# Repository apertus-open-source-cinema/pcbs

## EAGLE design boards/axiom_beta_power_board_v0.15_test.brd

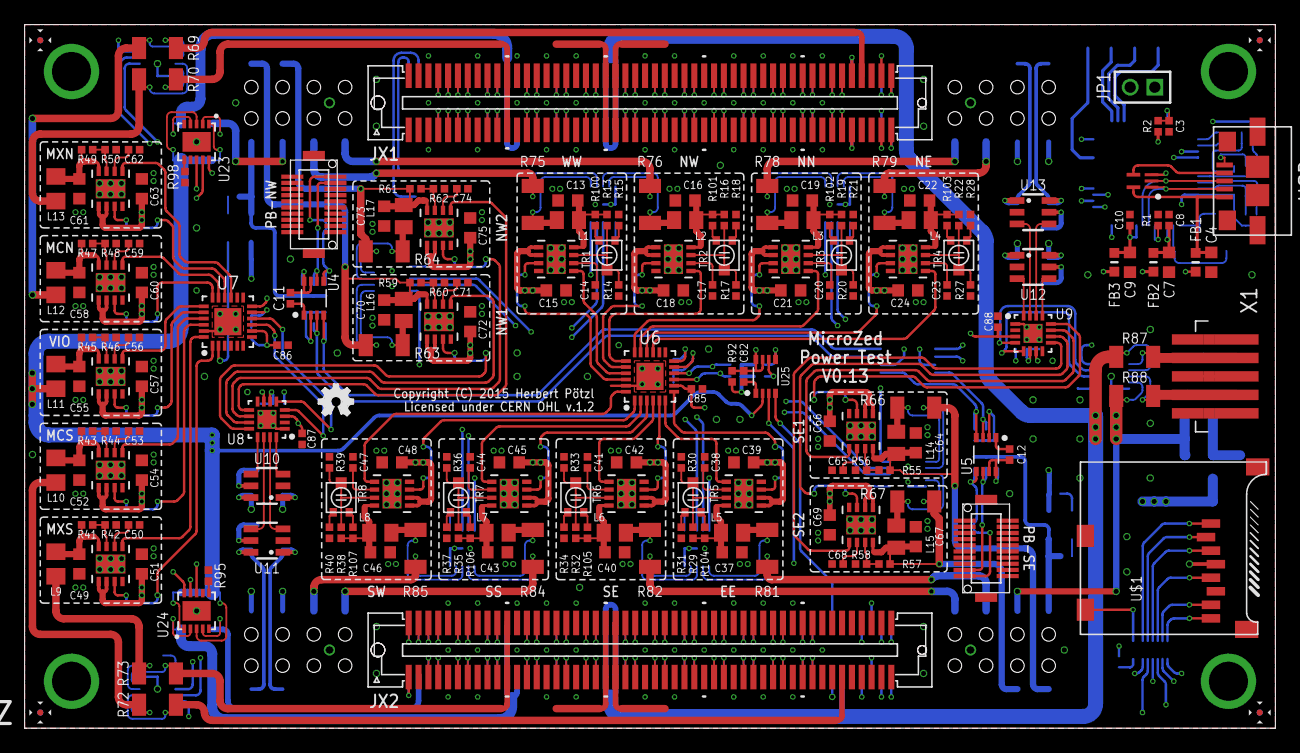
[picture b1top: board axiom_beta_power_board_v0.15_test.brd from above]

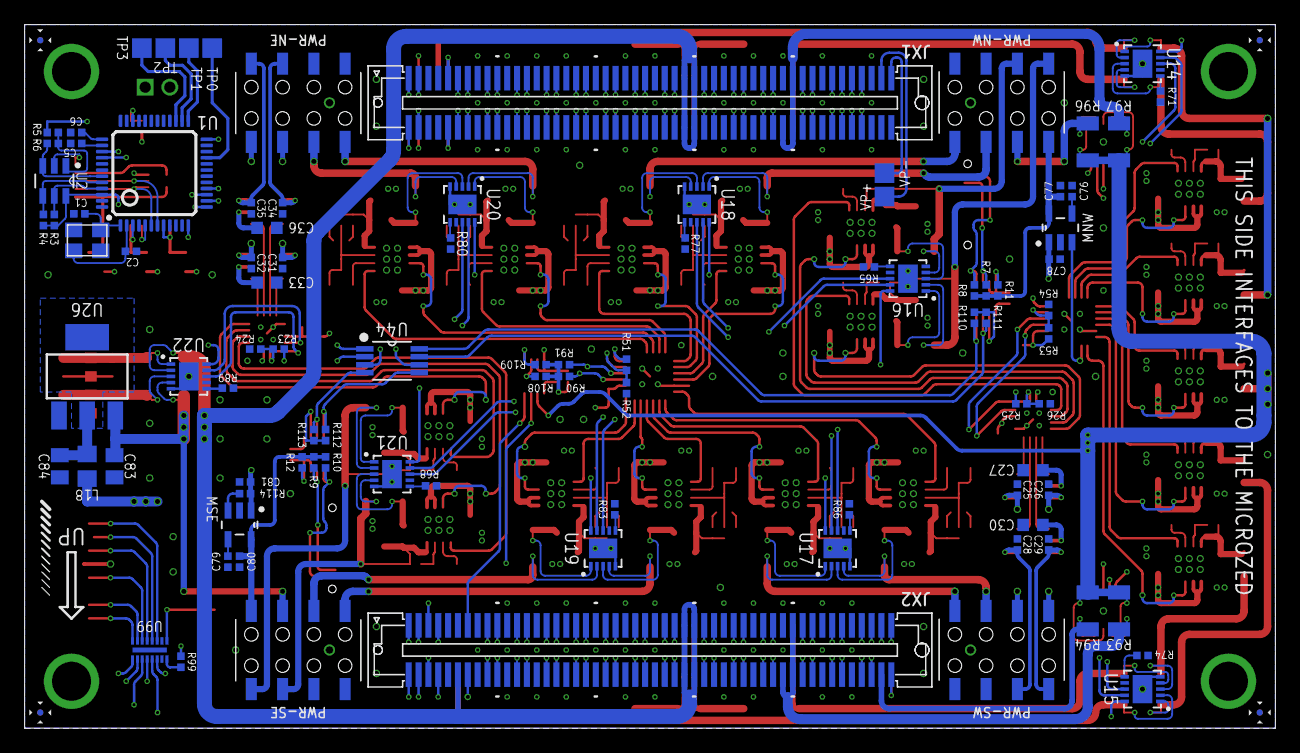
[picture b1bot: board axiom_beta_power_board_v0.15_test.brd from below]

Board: 4 copper layers, 101.6 x 57.1 mm, 298 parts (94 on the bottom side), 361 nets.

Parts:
BETA: µZ-FCI-SOCKET-NOHOLES-R; µZ-SOCKET-NOHOLES-R
C1, C2, C11, C12, C14, C17, C20, C23, C38, C41, C44, C47, C50, C53, C56, C59, C62, C65, C68, C71, C74, C76, C77, C78, C79, C80, C81, C82, C85, C86, C87, C88: 0402-B
C3: 10n; 0402-B
C4: 100n; 0603-B
C5, C6, C8, C10: 100n; 0402-B
C7, C9: 4µ7; 0603-B
C13, C15, C16, C18, C19, C21, C22, C24, C37, C39, C40, C42, C43, C45, C46, C48, C49, C51, C52, C54, C55, C57, C58, C60, C61, C63, C64, C66, C67, C69, C70, C72, C73, C75: 0603-B
C25, C26, C28, C29, C31, C32, C34, C35: 1µ; 0402-B
C27, C30, C33, C36: 1µ; 0603-B
C83, C84: 0805-B
EE: MCP1727-ADJE/MF; DFN65P300X300X100-9N
FB1, FB2, FB3: 600R; _0603MP
JP1: 1X02M
L1, L2, L3, L4, L5, L6, L7, L8, L14, L15, L16, L17: 0805-B
L9, L10, L11, L12, L13, L18: 0805-A
LOGO1: OSHW_LOGO_FILLX0100-NT; OSHW_FILLX100_NOTEXT
MCN: MCP1727-ADJE/MF; DFN65P300X300X100-9N
MCS: MCP1727-ADJE/MF; DFN65P300X300X100-9N
MNW: SPX3819M5-L; SOT95P280X145-5N
MSE: SPX3819M5-L; SOT95P280X145-5N
MXN: MCP1727-ADJE/MF; DFN65P300X300X100-9N
MXS: MCP1727-ADJE/MF; DFN65P300X300X100-9N
NE: MCP1727-ADJE/MF; DFN65P300X300X100-9N
NN: MCP1727-ADJE/MF; DFN65P300X300X100-9N
NW, NW1, NW2: MCP1727-ADJE/MF; DFN65P300X300X100-9N
PB-NW: DF12(XX)-20DP-0.5V
PB-SE: DF12(XX)-20DP-0.5V
PWR-NE: PINRC-2X04; R2X04
PWR-NW: PINRC-2X04; R2X04
PWR-SE: PINRC-2X04; R2X04
PWR-SW: PINRC-2X04; R2X04
Q1: SMD-4P-2G-3.2X2.5; ABM8G
R1: 12k; 0402-B
R2, R3, R4, R5: 10k; 0402-B
R6: 2k; 0402-B
R7, R8, R9, R10, R11, R12, R13, R14, R15, R16, R17, R18, R19, R20, R21, R22, R23, R24, R25, R26, R27, R28, R29, R30, R31, R32, R33, R34, R35, R36, R37, R38, R39, R40, R41, R42, R43, R44, R45, R46, R47, R48, R49, R50, R51, R52, R53, R54, R55, R56, R57, R58, R59, R60, R61, R62, R65, R68, R71, R74, R77, R80, R83, R86, R89, R90, R91, R92, R95, R98, R99, R100, R101, R102, R103, R104, R105, R106, R107, R108, R109, R110, R111, R112, R113, R114: 0402-B
R63, R64, R66, R67, R69, R70, R72, R73, R75, R76, R78, R79, R81, R82, R84, R85, R87, R88, R93, R94, R96, R97: 1206-B
SE, SE1, SE2: MCP1727-ADJE/MF; DFN65P300X300X100-9N
SS: MCP1727-ADJE/MF; DFN65P300X300X100-9N
SW: MCP1727-ADJE/MF; DFN65P300X300X100-9N
TP0, TP1, TP2, TP3: TPTP16SQ; TP16SQ
TR1, TR2, TR3, TR4, TR5, TR6, TR7, TR8: PVZ2A; TRIM-PVZ2A
U1: FT232H; LQFP48
U2: 93LC46BT-I/OT; SOT95P280X145-6N
U3: TPD3E001DRLR; SOT50P160X60-5N
U4, U5, U25: GTL2002DC; VSSOP-8
U6, U7: QFN50P400X400X80-25N
U8, U9: MCP23009-E/MG; QFN50P300X300X80-17N
U10, U11, U12, U13: SOT23-6
U14, U15, U16, U17, U18, U19, U20, U21, U22, U23, U24: PAC1720; DFN3X3_10LEAD
U26: LD1117S; SOT-223
U44: PCA9540BDP; SOP65P490X110-8N
U99: IP4251CZ16-8-TTL; SON40P135X330X55-17N
U$1: MICRO-SD-2CD; TF-MICRO-SD_PP2
USB: 5_USB_3S; MICRO-AB-H-SMT
VIO: MCP1727-ADJE/MF; DFN65P300X300X100-9N
VP+: TPTP16SQ; TP16SQ
VP-: TPTP16SQ; TP16SQ
WW: MCP1727-ADJE/MF; DFN65P300X300X100-9N
X1: PICO-SPOX-5
ZED: µZ-FCI-CONONLY; µZ-CONONLY

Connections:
AB_SCL: U25.4, ZED.113
AB_SCL': R109.2, U25.5, U44.1
AB_SDA: U25.3, ZED.114
AB_SDA': R108.2, U25.6, U44.2
A_SCL: PB-NW.2, R8.2, U4.5
A_SCL': R110.2, U4.4, U44.8
A_SDA: PB-NW.4, R7.2, U4.6
A_SDA': R111.2, U4.3, U44.7
BANK13_00_N: BETA.87, ZED.87
BANK13_00_P: BETA.89, ZED.89
BANK13_01_N: BETA.90, ZED.90
BANK13_01_P: BETA.88, ZED.88
BANK13_02_N: BETA.91, ZED.91
BANK13_02_P: BETA.93, ZED.93
BANK13_03_N: BETA.92, ZED.92
BANK13_03_P: BETA.94, ZED.94
BANK13_04_N: BETA.193, ZED.193
BANK13_04_P: BETA.195, ZED.195
BANK13_05_N: BETA.196, ZED.196
BANK13_05_P: BETA.194, ZED.194
BANK13_06_N: BETA.199, ZED.199
BANK13_06_P: BETA.197, ZED.197
BANK13_SE_0: BETA.200, ZED.200
BETA_5V: R88.1, U22.3, X1.4, X1.4A
BETA_5V': C15.1, C18.1, C21.1, C24.1, C27.1, C30.1, C33.1, C36.1, C39.1, C42.1, C45.1, C48.1, C51.1, C54.1, C57.1, C60.1, C63.1, C66.1, C69.1, C72.1, C75.1, C78.1, C81.1, C83.1, EE.1, EE.2, MCN.1, MCN.2, MCS.1, MCS.2, MNW.1, MSE.1, MXN.1, MXN.2, MXS.1, MXS.2, NE.1, NE.2, NN.1, NN.2, NW.1, NW.2, NW1.1, NW1.2, NW2.1, NW2.2, PWR-SE.6, R88.2, R114.1, SE.1, SE.2, SE1.1, SE1.2, SE2.1, SE2.2, SS.1, SS.2, SW.1, SW.2, U10.5, U11.5, U12.5, U13.5, U22.4, U26.3, VIO.1, VIO.2, WW.1, WW.2
BETA_TDO: BETA.3, JP1.2
B_SCL: PB-SE.2, R10.2, U5.5
B_SCL': R112.2, U5.4, U44.5
B_SDA: PB-SE.4, R9.2, U5.6
B_SDA': R113.2, U5.3, U44.4
CD: U99.1, U$1.CD1
CLK: U99.6, U$1.5
CMD: U99.5, U$1.3
CSO_N_V: BETA.7, R69.2, U14.2
CSO_N_V': L12.2, R69.1, U14.1
CSO_S_V: BETA.112, R72.2, U15.2
CSO_S_V': L10.2, R72.1, U15.1
DAT0: U99.7, U$1.7
DAT1: U99.8, U$1.8
DAT2: U99.3, U$1.1
DAT3: U99.4, U$1.2
EE_CLK1: R4.1, U1.44, U2.4
EE_CS1: R3.1, U1.45, U2.5
EE_DATA1: R6.2, U1.43, U2.3
EN1: U8.13, U10.4
EN1B: U9.13, U12.4
EN2: U8.14, U11.4
EN2B: U9.14, U13.4
EN3: U8.16, U10.3
EN3B: U9.16, U12.3
EN4: U8.15, U11.3
EN4B: U9.15, U13.3
EX_N_V: BETA.57, BETA.58
EX_S_V: BETA.157, BETA.158
E_I2C_V: C34.1, PWR-NE.6, U13.1
E_SPI_V: C35.1, PWR-NE.8, U13.6
E_VE: PWR-SE.4, R81.2, U19.2
E_VE': L5.2, R81.1, U19.1
FTDI_D_N: U1.6, U3.1, USB.2
FTDI_D_P: U1.7, U3.2, USB.3
FTDI_TCK: BETA.1, U1.13, ZED.1
FTDI_TDI: BETA.4, U1.14
FTDI_TDO: U1.15, ZED.3
FTDI_TMS: BETA.2, U1.16, ZED.2
GND: BETA.15, BETA.16, BETA.21, BETA.22, BETA.27, BETA.28, BETA.33, BETA.34, BETA.39, BETA.40, BETA.45, BETA.46, BETA.51, BETA.52, BETA.65, BETA.66, BETA.71, BETA.72, BETA.77, BETA.85, BETA.86, BETA.95, BETA.96, BETA.115, BETA.116, BETA.121, BETA.122, BETA.127, BETA.128, BETA.133, BETA.134, BETA.139, BETA.140, BETA.145, BETA.146, BETA.151, BETA.152, BETA.165, BETA.166, BETA.171, BETA.172, BETA.177, BETA.185, BETA.186, BETA.191, BETA.192, C1.2, C2.2, C3.2, C4.2, C5.2, C6.2, C7.2, C8.2, C9.2, C10.2, C11.2, C12.2, C13.2, C14.2, C15.2, C16.2, C17.2, C18.2, C19.2, C20.2, C21.2, C22.2, C23.2, C24.2, C25.2, C26.2, C27.2, C28.2, C29.2, C30.2, C31.2, C32.2, C33.2, C34.2, C35.2, C36.2, C37.2, C38.2, C39.2, C40.2, C41.2, C42.2, C43.2, C44.2, C45.2, C46.2, C47.2, C48.2, C49.2, C50.2, C51.2, C52.2, C53.2, C54.2, C55.2, C56.2, C57.2, C58.2, C59.2, C60.2, C61.2, C62.2, C63.2, C64.2, C65.2, C66.2, C67.2, C68.2, C69.2, C70.2, C71.2, C72.2, C73.2, C74.2, C75.2, C76.2, C77.2, C78.2, C79.2, C80.2, C81.2, C82.2, C83.2, C84.2, C85.2, C86.2, C87.2, C88.2, EE.4, EE.9, MCN.4, MCN.9, MCS.4, MCS.9, MNW.2, MSE.2, MXN.4, MXN.9, MXS.4, MXS.9, NE.4, NE.9, NN.4, NN.9, NW.4, NW.9, NW1.4, NW1.9, NW2.4, NW2.9, PB-NW.6, PB-NW.7, PB-NW.10, PB-NW.13, PB-NW.18, PB-SE.6, PB-SE.7, PB-SE.10, PB-SE.13, PB-SE.18, PWR-NE.2, PWR-NE.4, PWR-NW.1, PWR-NW.3, PWR-SE.1, PWR-SE.3, PWR-SW.2, PWR-SW.4, Q1.2, Q1.4, R1.1, R14.2, R15.2, R17.2, R18.2, R20.2, R21.2, R24.2, R26.2, R27.2, R28.2, R30.2, R31.2, R33.2, R34.2, R36.2, R37.2, R39.2, R40.2, R42.2, R44.2, R46.2, R48.2, R50.2, R52.2, R54.2, R56.2, R58.2, R60.2, R62.2, R65.2, R68.2, R71.2, R74.2, R77.2, R80.2, R83.2, R86.2, R89.2, R95.2, R98.2, SE.4, SE.9, SE1.4, SE1.9, SE2.4, SE2.9, SS.4, SS.9, SW.4, SW.9, U1.4, U1.9, U1.10, U1.11, U1.22, U1.23, U1.35, U1.36, U1.41, U1.47, U1.48, U2.2, U3.3, U4.1, U5.1, U6.23, U6.25, U7.23, U7.25, U8.1, U8.EP, U9.1, U9.EP, U10.2, U11.2, U12.2, U13.2, U14.5, U14.EPAD, U15.5, U15.EPAD, U16.5, U16.EPAD, U17.5, U17.EPAD, U18.5, U18.EPAD, U19.5, U19.EPAD, U20.5, U20.EPAD, U21.5, U21.EPAD, U22.5, U22.EPAD, U23.5, U23.EPAD, U24.5, U24.EPAD, U25.1, U26.1, U44.6, U99.17, U$1.6, U$1.CD2, USB.5, VIO.4, VIO.9, WW.4, WW.9, X1.1, X1.1A, X1.5, X1.5A, ZED.15, ZED.16, ZED.21, ZED.22, ZED.27, ZED.28, ZED.33, ZED.34, ZED.39, ZED.40, ZED.45, ZED.46, ZED.51, ZED.52, ZED.65, ZED.66, ZED.71, ZED.72, ZED.77, ZED.85, ZED.86, ZED.95, ZED.96, ZED.115, ZED.116, ZED.121, ZED.122, ZED.127, ZED.128, ZED.133, ZED.134, ZED.139, ZED.140, ZED.145, ZED.146, ZED.151, ZED.152, ZED.165, ZED.166, ZED.171, ZED.172, ZED.177, ZED.185, ZED.186, ZED.191, ZED.192
GPA0_C: NE.5, U6.15
GPA0_W: MXN.5, U7.15
GPA1_C: NE.3, U6.16
GPA1_W: MXN.3, U7.16
GPA2_C: NN.5, U6.17
GPA2_W: MCN.5, U7.17
GPA3_C: NN.3, U6.18
GPA3_W: MCN.3, U7.18
GPA4_C: NW.5, U6.19
GPA4_W: U7.19, VIO.5
GPA5_C: NW.3, U6.20
GPA5_W: U7.20, VIO.3
GPA6_C: U6.21, WW.5
GPA6_W: MCS.5, U7.21
GPA7_C: U6.22, WW.3
GPA7_W: MCS.3, U7.22
GPB0_C: SW.5, U6.24
GPB0_W: MXS.5, U7.24
GPB1_C: SW.3, U6.1
GPB1_W: MXS.3, U7.1
GPB2_C: SS.5, U6.2
GPB2_W: MNW.3, U7.2
GPB3_C: SS.3, U6.3
GPB4_C: SE.5, U6.4
GPB5_C: SE.3, U6.5
GPB6_C: EE.5, U6.6
GPB7_C: EE.3, U6.7
JTAG_V: C29.1, PWR-SW.8, U11.6
JX1_00_N: BETA.13, ZED.13
JX1_00_P: BETA.11, ZED.11
JX1_01_N: BETA.14, ZED.14
JX1_01_P: BETA.12, ZED.12
JX1_02_N: BETA.19, ZED.19
JX1_02_P: BETA.17, ZED.17
JX1_03_N: BETA.20, ZED.20
JX1_03_P: BETA.18, ZED.18
JX1_04_N: BETA.25, ZED.25
JX1_04_P: BETA.23, ZED.23
JX1_05_N: BETA.26, ZED.26
JX1_05_P: BETA.24, ZED.24
JX1_06_N: BETA.31, ZED.31
JX1_06_P: BETA.29, ZED.29
JX1_07_N: BETA.32, ZED.32
JX1_07_P: BETA.30, ZED.30
JX1_08_N: BETA.37, ZED.37
JX1_08_P: BETA.35, ZED.35
JX1_09_N: BETA.38, ZED.38
JX1_09_P: BETA.36, ZED.36
JX1_10_N: BETA.43, ZED.43
JX1_10_P: BETA.41, ZED.41
JX1_11_N: BETA.44, ZED.44
JX1_11_P: BETA.42, ZED.42
JX1_12_N: BETA.49, ZED.49
JX1_12_P: BETA.47, ZED.47
JX1_13_N: BETA.50, ZED.50
JX1_13_P: BETA.48, ZED.48
JX1_14_N: BETA.55, ZED.55
JX1_14_P: BETA.53, ZED.53
JX1_15_N: BETA.56, ZED.56
JX1_15_P: BETA.54, ZED.54
JX1_16_N: BETA.63, ZED.63
JX1_16_P: BETA.61, ZED.61
JX1_17_N: BETA.64, ZED.64
JX1_17_P: BETA.62, ZED.62
JX1_18_N: BETA.69, ZED.69
JX1_18_P: BETA.67, ZED.67
JX1_19_N: BETA.70, ZED.70
JX1_19_P: BETA.68, ZED.68
JX1_20_N: BETA.75, ZED.75
JX1_20_P: BETA.73, ZED.73
JX1_21_N: BETA.76, ZED.76
JX1_21_P: BETA.74, ZED.74
JX1_22_N: BETA.83, ZED.83
JX1_22_P: BETA.81, ZED.81
JX1_23_N: BETA.84, ZED.84
JX1_23_P: BETA.82, ZED.82
JX2_00_N: BETA.119, ZED.119
JX2_00_P: BETA.117, ZED.117
JX2_01_N: BETA.120, ZED.120
JX2_01_P: BETA.118, ZED.118
JX2_02_N: BETA.125, ZED.125
JX2_02_P: BETA.123, ZED.123
JX2_03_N: BETA.126, ZED.126
JX2_03_P: BETA.124, ZED.124
JX2_04_N: BETA.131, ZED.131
JX2_04_P: BETA.129, ZED.129
JX2_05_N: BETA.132, ZED.132
JX2_05_P: BETA.130, ZED.130
JX2_06_N: BETA.137, ZED.137
JX2_06_P: BETA.135, ZED.135
JX2_07_N: BETA.138, ZED.138
JX2_07_P: BETA.136, ZED.136
JX2_08_N: BETA.143, ZED.143
JX2_08_P: BETA.141, ZED.141
JX2_09_N: BETA.144, ZED.144
JX2_09_P: BETA.142, ZED.142
JX2_10_N: BETA.149, ZED.149
JX2_10_P: BETA.147, ZED.147
JX2_11_N: BETA.150, ZED.150
JX2_11_P: BETA.148, ZED.148
JX2_12_N: BETA.155, ZED.155
JX2_12_P: BETA.153, ZED.153
JX2_13_N: BETA.156, ZED.156
JX2_13_P: BETA.154, ZED.154
JX2_14_N: BETA.163, ZED.163
JX2_14_P: BETA.161, ZED.161
JX2_15_N: BETA.164, ZED.164
JX2_15_P: BETA.162, ZED.162
JX2_16_N: BETA.169, ZED.169
JX2_16_P: BETA.167, ZED.167
JX2_17_N: BETA.170, ZED.170
JX2_17_P: BETA.168, ZED.168
JX2_18_N: BETA.175, ZED.175
JX2_18_P: BETA.173, ZED.173
JX2_19_N: BETA.176, ZED.176
JX2_19_P: BETA.174, ZED.174
JX2_20_N: BETA.183, ZED.183
JX2_20_P: BETA.181, ZED.181
JX2_21_N: BETA.184, ZED.184
JX2_21_P: BETA.182, ZED.182
JX2_22_N: BETA.189, ZED.189
JX2_22_P: BETA.187, ZED.187
JX2_23_N: BETA.190, ZED.190
JX2_23_P: BETA.188, ZED.188
MP-NW-1': L16.2, R63.1, U16.1
MP-NW-2': L17.2, R64.1, U16.3
MP-SE-1': L14.2, R66.1, U21.1
MP-SE-2': L15.2, R67.1, U21.3
M_V_NW: C77.1, MNW.5, PWR-NW.8, R7.1, R8.1, R11.1
M_V_SE: C80.1, MSE.5, PWR-SE.8, R9.1, R10.1, R12.1
unnamed: C49.1, L9.1, MXS.8, R41.1
unnamed: R77.1, U18.6
unnamed: C11.1, R11.2, U4.7, U4.8
unnamed: C12.1, R12.2, U5.7, U5.8
unnamed: C13.1, L1.1, R13.1, R100.2, WW.8
unnamed: TP1.TP, U1.25
unnamed: TP2.TP, U1.26
unnamed: R95.1, U24.6
unnamed: R13.2, R14.1, TR1.2, WW.7
unnamed: R15.1, TR1.1
unnamed: MXS.7, R41.2, R42.1
unnamed: C50.1, MXS.6
unnamed: C64.1, L14.1, R55.1, SE1.8
unnamed: R55.2, R56.1, SE1.7
unnamed: VP+.TP, ZED.97
unnamed: VP-.TP, ZED.99
unnamed: R98.1, U23.6
unnamed: TP3.TP, U1.27
unnamed: R99.2, U99.16
unnamed: C14.1, WW.6
unnamed: C65.1, SE1.6
unnamed: C67.1, L15.1, R57.1, SE2.8
unnamed: TP0.TP, U1.21
unnamed: R5.1, R6.1, U2.1
unnamed: C1.1, Q1.1, U1.1
unnamed: C2.1, Q1.3, U1.2
unnamed: C3.1, R2.1, U1.34
unnamed: R1.2, U1.5
unnamed: U3.4, USB.4
unnamed: R23.2, R24.1, U9.6
unnamed: R25.2, R26.1, U8.6
unnamed: R100.1, TR1.3
unnamed: C16.1, L2.1, NW.8, R16.1, R101.2
unnamed: NW.7, R16.2, R17.1, TR2.2
unnamed: R18.1, TR2.1
unnamed: C17.1, NW.6
unnamed: R57.2, R58.1, SE2.7
unnamed: C68.1, SE2.6
unnamed: R80.1, U20.6
unnamed: C19.1, L3.1, NN.8, R19.1, R102.2
unnamed: NN.7, R19.2, R20.1, TR3.2
unnamed: R101.1, TR2.3
unnamed: C20.1, NN.6
unnamed: C70.1, L16.1, NW1.8, R59.1
unnamed: NW1.7, R59.2, R60.1
unnamed: R83.1, U19.6
unnamed: C22.1, L4.1, NE.8, R22.1, R103.2
unnamed: NE.7, R22.2, R27.1, TR4.2
unnamed: R21.1, TR3.1
unnamed: C23.1, NE.6
unnamed: C71.1, NW1.6
unnamed: C73.1, L17.1, NW2.8, R61.1
unnamed: R86.1, U17.6
unnamed: C37.1, EE.8, L5.1, R29.1, R104.2
unnamed: EE.7, R29.2, R30.1, TR5.2
unnamed: R102.1, TR3.3
unnamed: C38.1, EE.6
unnamed: NW2.7, R61.2, R62.1
unnamed: C74.1, NW2.6
unnamed: R28.1, TR4.1
unnamed: R65.1, U16.6
unnamed: C40.1, L6.1, R32.1, R105.2, SE.8
unnamed: R32.2, R33.1, SE.7, TR6.2
unnamed: R103.1, TR4.3
unnamed: C41.1, SE.6
unnamed: C82.1, R92.2, U25.7, U25.8
unnamed: R31.1, TR5.1
unnamed: C43.1, L7.1, R35.1, R106.2, SS.8
unnamed: R35.2, R36.1, SS.7, TR7.2
unnamed: R104.1, TR5.3
unnamed: C44.1, SS.6
unnamed: R34.1, TR6.1
unnamed: R68.1, U21.6
unnamed: C46.1, L8.1, R38.1, R107.2, SW.8
unnamed: R38.2, R39.1, SW.7, TR8.2
unnamed: R105.1, TR6.3
unnamed: C47.1, SW.6
unnamed: R37.1, TR7.1
unnamed: R71.1, U14.6
unnamed: R106.1, TR7.3
unnamed: R74.1, U15.6
unnamed: C52.1, L10.1, MCS.8, R43.1
unnamed: MCS.7, R43.2, R44.1
unnamed: C53.1, MCS.6
unnamed: R40.1, TR8.1
unnamed: R89.1, U22.6
unnamed: C55.1, L11.1, R45.1, VIO.8
unnamed: R45.2, R46.1, VIO.7
unnamed: C56.1, VIO.6
unnamed: R107.1, TR8.3
unnamed: C58.1, L12.1, MCN.8, R47.1
unnamed: MCN.7, R47.2, R48.1
unnamed: C59.1, MCN.6
unnamed: C76.1, MNW.4
unnamed: C61.1, L13.1, MXN.8, R49.1
unnamed: MXN.7, R49.2, R50.1
unnamed: C62.1, MXN.6
unnamed: R51.2, R52.1, U6.11
unnamed: R53.2, R54.1, U7.11
unnamed: C79.1, MSE.4
N_I2C_V: C32.1, PWR-NE.7, U12.6
N_SPI_V: C31.1, PWR-NE.5, U12.1
N_VE: PWR-NE.3, R79.2, U20.4
N_VE': L4.2, R79.1, U20.3
N_VN: PWR-NE.1, R78.2, U20.2
N_VN': L3.2, R78.1, U20.1
N_VW: PWR-NW.2, R76.2, U18.4
N_VW': L2.2, R76.1, U18.3
PCIE_N_5V: BETA.59, BETA.60
PCIE_N_V: BETA.79, BETA.80, R70.2, U14.4
PCIE_N_V': L13.2, R70.1, U14.3
PCIE_S_5V: BETA.159, BETA.160
PCIE_S_V: BETA.179, BETA.180, R73.2, U15.4
PCIE_S_V': L9.2, R73.1, U15.3
PCIE_VCCIO: PWR-NW.6, R96.2, U23.2
PMOD_D0: U99.9, ZED.101
PMOD_D1: U99.10, ZED.102
PMOD_D2: U99.12, ZED.103
PMOD_D3: U99.11, ZED.104
PMOD_D6: U99.14, ZED.107
PMOD_D7: U99.13, ZED.108
PMOD_SCL: R90.2, U6.9, U7.9, U8.4, U9.4, U14.9, U15.9, U16.9, U17.9, U18.9, U19.9, U20.9, U21.9, U22.9, U23.9, U24.9, ZED.105
PMOD_SDA: R91.2, U6.10, U7.10, U8.5, U9.5, U14.8, U15.8, U16.8, U17.8, U18.8, U19.8, U20.8, U21.8, U22.8, U23.8, U24.8, ZED.106
REGOUT: C84.1, L18.1, U26.2, U26.TER
SE_0: BETA.9, ZED.9
SE_1: BETA.10, ZED.10
SH_NW_V1: PWR-NW.7, R63.2, U16.2
SH_NW_V2: PWR-NW.5, R64.2, U16.4
SH_SE_V1: PWR-SE.7, R66.2, U21.2
SH_SE_V2: PWR-SE.5, R67.2, U21.4
S_I2C_V: C26.1, PWR-SW.7, U10.6
S_SPI_V: C25.1, PWR-SW.5, U10.1
S_VE: PWR-SE.2, R82.2, U19.4
S_VE': L6.2, R82.1, U19.3
S_VS: PWR-SW.1, R84.2, U17.2
S_VS': L7.2, R84.1, U17.1
S_VW: PWR-SW.3, R85.2, U17.4
S_VW': L8.2, R85.1, U17.3
U26_PWRGD: SE1.5, U9.11
U26_SHDN: SE1.3, U9.12
U27_PWRGD: SE2.5, U9.9
U27_SHDN: SE2.3, U9.10
U28_PWRGD: NW1.5, U8.11
U28_SHDN: NW1.3, U8.12
U29_PWRGD: NW2.5, U8.9
U29_SHDN: NW2.3, U8.10
U40_EN: MSE.3, R114.2
VBUS: C4.1, FB1.1, U3.5, USB.1
VCC: C85.1, C86.1, C87.1, C88.1, L18.2, R23.1, R25.1, R51.1, R53.1, R90.1, R91.1, R92.1, R99.1, R108.1, R109.1, R110.1, R111.1, R112.1, R113.1, U4.2, U5.2, U6.8, U6.12, U7.8, U7.12, U8.3, U8.7, U9.3, U9.7, U14.10, U15.10, U16.10, U17.10, U18.10, U19.10, U20.10, U21.10, U22.10, U23.10, U24.10, U44.3, U$1.4
VCCA: C6.1, U1.37
VCCD: FB2.1, FB3.1, R2.2, R3.2, R4.2, R5.2, U1.12, U1.24, U1.39, U1.46, U2.6
VCCIO: L11.2, R93.1, R94.1, R96.1, R97.1, U23.1, U23.3, U24.1, U24.3, U25.2
VCCO_13: R94.2, U24.4, ZED.198
VCCO_34: R97.2, U23.4, ZED.78, ZED.79, ZED.80
VCCO_35: R93.2, U24.2, ZED.178, ZED.179, ZED.180
VCORE: C5.1, U1.38
VIN: X1.3, X1.3A
VPHY: C7.1, C8.1, FB2.2, U1.3
VPLL: C9.1, C10.1, FB3.2, U1.8
VREGIN: FB1.2, U1.40
W_I2C_V: C28.1, PWR-SW.6, U11.1
W_VW: PWR-NW.4, R75.2, U18.2
W_VW': L1.2, R75.1, U18.1
ZED_5V: R87.1, U22.1, X1.2, X1.2A
ZED_5V': R87.2, U22.2, ZED.57, ZED.58, ZED.59, ZED.60, ZED.112, ZED.157, ZED.158, ZED.159, ZED.160
ZED_TDI: JP1.1, ZED.4

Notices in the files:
boards/axiom_beta_power_board_v0.15_test.brd:
Copyright (C) 2015 Herbert Pötzl
Licensed under CERN OHL v.1.2
parts and their libraries:
microbuilder: This work is placed in the public domain, and may be freely used for commercial and non-commercial work with the following conditions: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
